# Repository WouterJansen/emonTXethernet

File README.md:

# emonTXethernet

This repository is a collection of files used to correctly setup and use a EmonTX Shield on a Arduino. It uses a Ethernet Shield for the communication instead of the usual radio seen on EmonTX. 

This repository has the following items:
* The firmware sketch for a Arduino to measure the EmonTX CT sensor inputs and send them with a HTTP GET request to EmonCMS.
* 3D printing files for a case that holds a Arduino Uno with a mounted standard Ethernet Shield and EmonTX Shield.
* Simplistic OpenHab instructions for correctly reading the EmonCMS MQTT messages and display them on your sitemap.
* Custom PCB Board files to make a simplified EmonTX Board soley focused on the CT input sensors and 9V AC-AC adapter. Without all components for UART or radio communication. 

This is all based on original work by others. See the invidiual files for more credit information. Mostly OpenEnergyMonitor is responsible for all the posibilities seen here. https://openenergymonitor.org/

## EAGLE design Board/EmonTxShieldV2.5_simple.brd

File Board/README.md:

# EmonTX Simplified PCB Board

Fully based on the original by OpenEnergyMonitor. Found here: https://github.com/openenergymonitor/emontx-shield/tree/master/hardware/emontx-shield-smt

Changes include removing all components not connected to the working of the CT Sensor measurements or 9V AC-AC measurement. Same size as other one to increase compatability. 

Making this board is absolutly not required. EmonTX Shield from OpenEnergyMonitor is perfect and even offers the option to also use the radio module. 

## Components 
Components required to build and solder it yourself. 
* 5x 10 µF STM capacitors, package 0603
* 10x 470 KΩ resistors, package 0603
* 1x 120 KΩ resistor, package 0603
* 1x 10 KΩ resistor, package 0603
* 1x 1 KΩ resistor, package 0603
* 8x 33 Ω resistors, package 1206
* 1x DC Power connector, 5.5x2.1mm, like these: https://www.banggood.com/50pcs-DC-005-3Pin-Black-DC-Power-Jack-Socket-Connector-5_52_1mm-p-1127042.html?rmmds=myorder&cur_warehouse=CN
* 4x 3.5mm Stereo jack connector: like these: https://lcsc.com/product-detail/Audio-Connectors_Headphone-interface_C16684.html
* 1x green LED, like these: https://lcsc.com/product-detail/Light-Emitting-Diodes-LED_AVAGO_HSMQ-C191_HSMQ-C191_C188732.html
* Headers

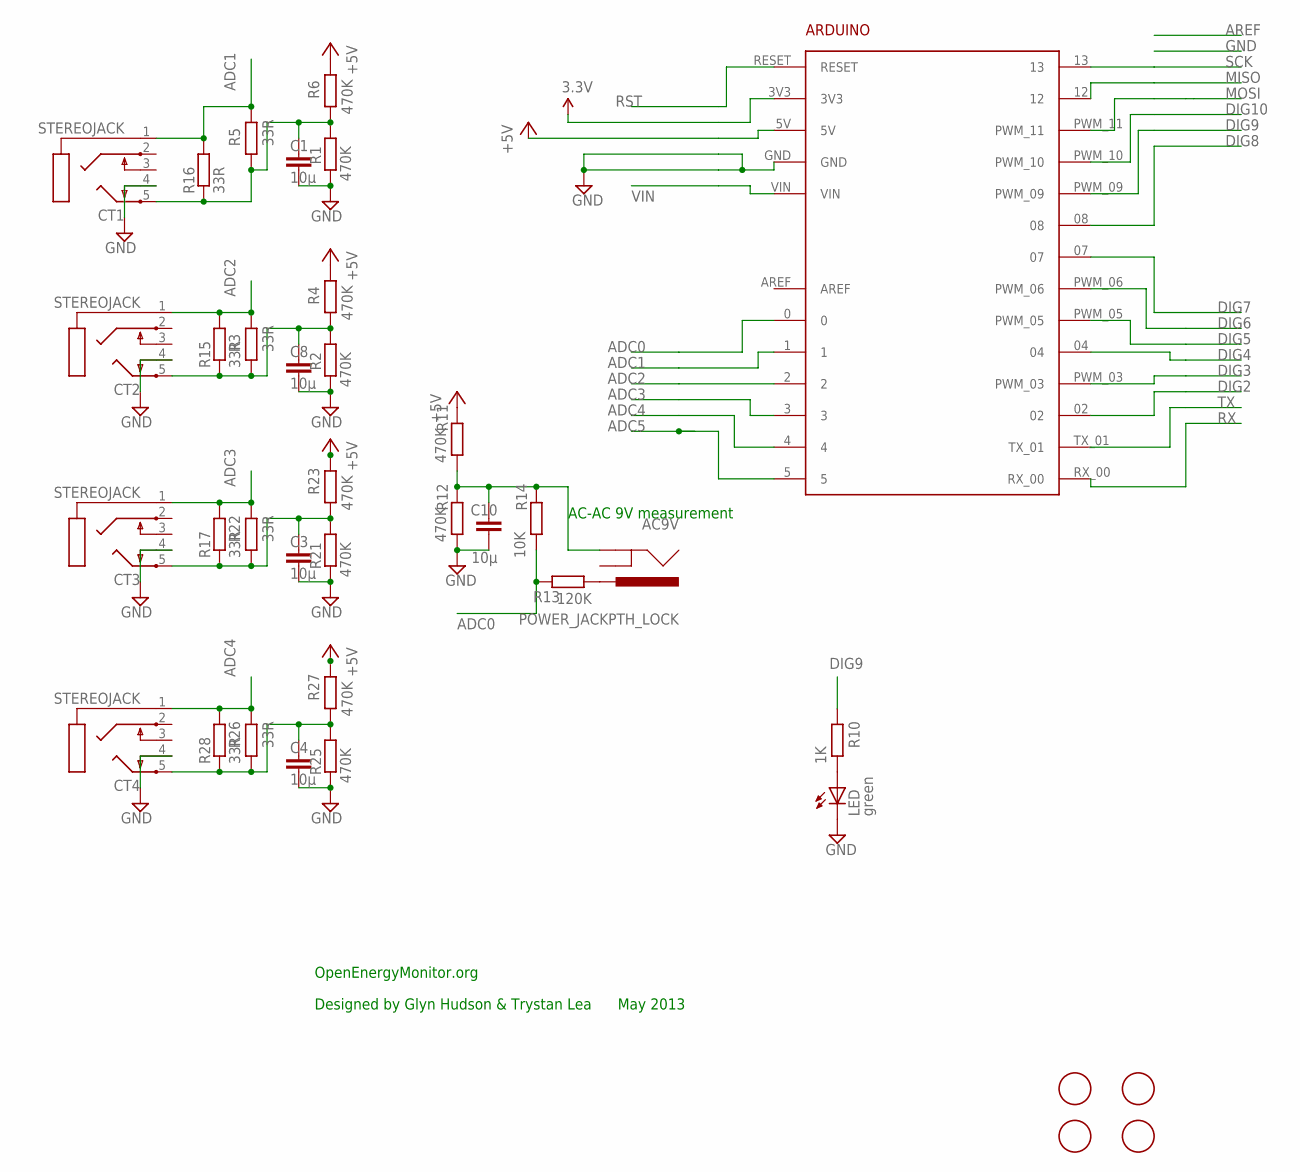
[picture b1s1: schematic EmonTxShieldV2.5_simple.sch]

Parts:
AC9V: POWER_JACKPTH_LOCK; POWER_JACK_PTH_LOCK
ARDUINO1: ARDUINO2
C1, C3, C4, C8, C10: 10µ; C0603
CT1, CT2, CT3, CT4: STEREOJACK; STX3100
LED: green; CHIPLED_0805
R1, R2, R4, R6, R11, R12, R21, R23, R25, R27: 470K; R0603
R3, R5, R22, R26: 33R; 0204/7
R10: 1K; R0603
R13: 120K; R0603
R14: 10K; R0603
R15, R16, R17, R28: 33R; R1206
U$1, U$3, U$4, U$5: FIDUCIAL; FIDUCIAL_1MM

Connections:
3.3V: ARDUINO1.3V3
+5V: ARDUINO1.5V, R4.2, R6.2, R11.2, R23.2, R27.2
ADC0: ARDUINO1.0, R13.2, R14.1
ADC1: ARDUINO1.1, CT1.1, R5.2, R16.2
ADC2: ARDUINO1.2, CT2.1, R3.2, R15.2
ADC3: ARDUINO1.3, CT3.1, R17.2, R22.2
ADC4: ARDUINO1.4, CT4.1, R26.2, R28.2
ADC5: ARDUINO1.5
DIG2: ARDUINO1.02
DIG3: ARDUINO1.PWM_03
DIG4: ARDUINO1.04
DIG5: ARDUINO1.PWM_05
DIG6: ARDUINO1.PWM_06
DIG7: ARDUINO1.07
DIG8: ARDUINO1.08
DIG9: ARDUINO1.PWM_09, R10.2
DIG10: ARDUINO1.PWM_10
GND: ARDUINO1.GND, C1.2, C3.2, C4.2, C8.2, C10.2, CT1.4, CT2.4, CT3.4, CT4.4, LED.C, R1.2, R2.2, R12.1, R21.2, R25.2
MISO: ARDUINO1.12
MOSI: ARDUINO1.PWM_11
unnamed: C3.1, CT3.5, R17.1, R21.1, R22.1, R23.1
unnamed: C4.1, CT4.5, R25.1, R26.1, R27.1, R28.1
unnamed: AC9V.PWR, R13.1
unnamed: C8.1, CT2.5, R2.1, R3.1, R4.1, R15.1
unnamed: AC9V.GND, C10.1, R11.1, R12.2, R14.2
unnamed: C1.1, CT1.5, R1.1, R5.1, R6.1, R16.1
unnamed: LED.A, R10.1
RST: ARDUINO1.RESET
RX: ARDUINO1.RX_00
SCK: ARDUINO1.13
TX: ARDUINO1.TX_01
VIN: ARDUINO1.VIN

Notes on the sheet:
AC-AC 9V measurement
OpenEnergyMonitor.org
Designed by Glyn Hudson & Trystan Lea May 2013

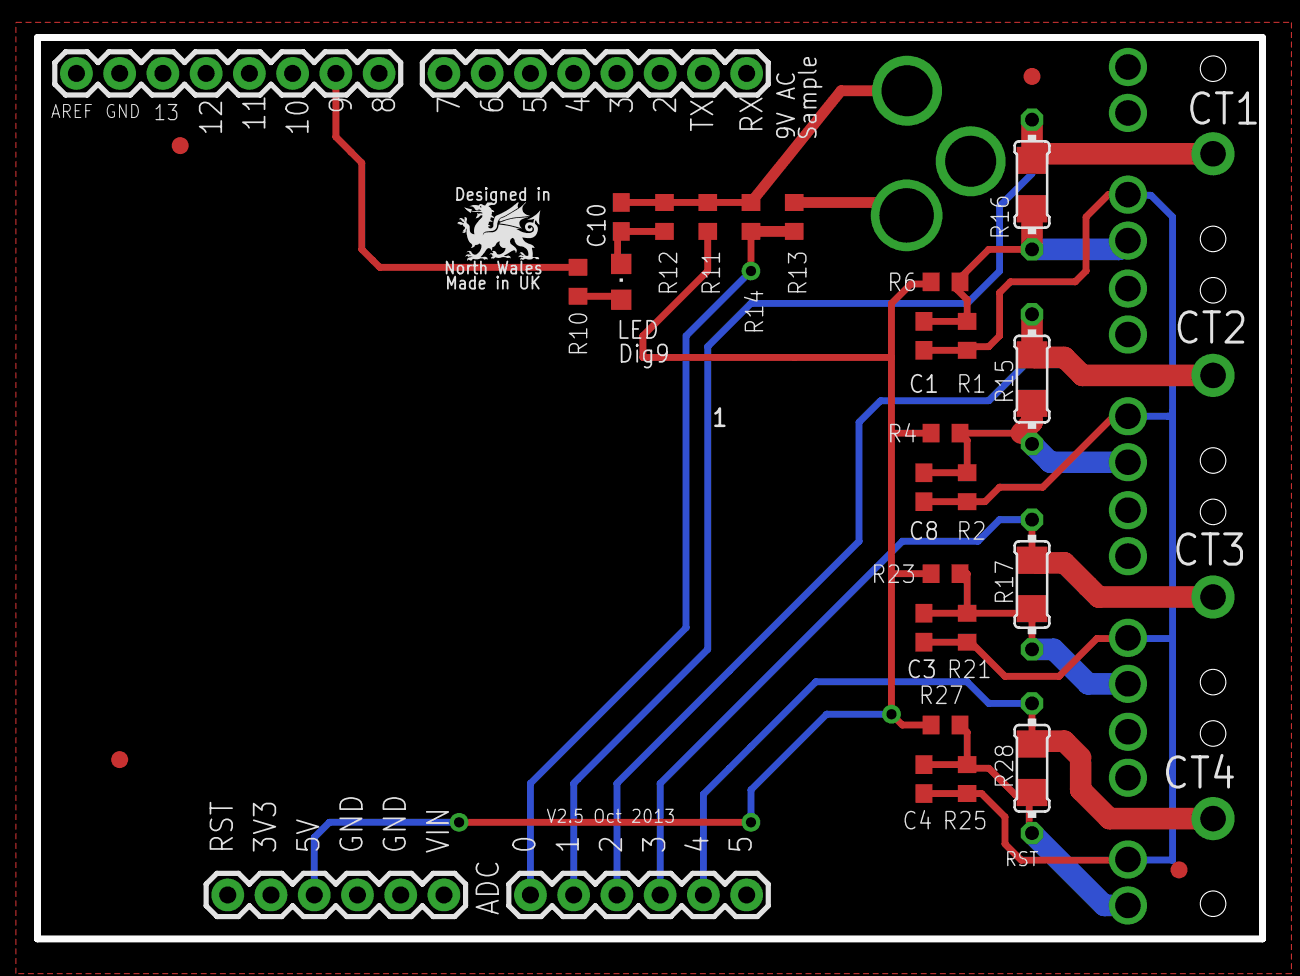
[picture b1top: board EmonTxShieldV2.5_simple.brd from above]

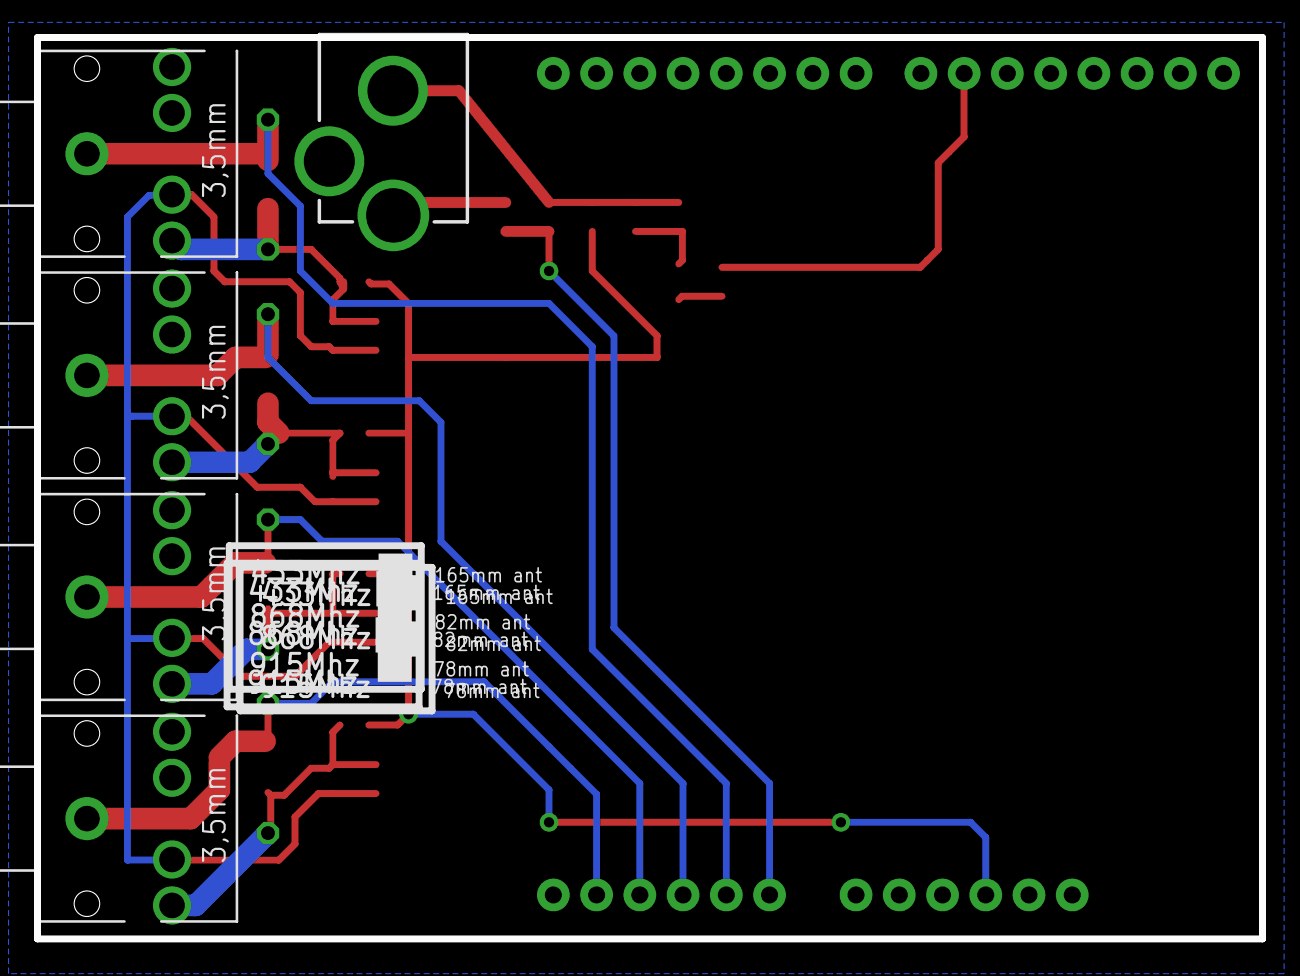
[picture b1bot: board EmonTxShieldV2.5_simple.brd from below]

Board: 2 copper layers, 72.0 x 53.0 mm, 37 parts (5 on the bottom side), 15 nets.

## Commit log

2018-06-12 Added readme's and arduino firmware
    Added full arduino firmware and readme files to be edited alter
2018-06-12 Updated firmware
    Fixed error in arduino firmware
2018-06-12 Auto stash before merge of "master" and "origin/master"
2018-06-12 Added board and case files. Updated board readme
    Added board and case files. Updated board readme
2018-06-12 Added stl case files
    Added stl case files
